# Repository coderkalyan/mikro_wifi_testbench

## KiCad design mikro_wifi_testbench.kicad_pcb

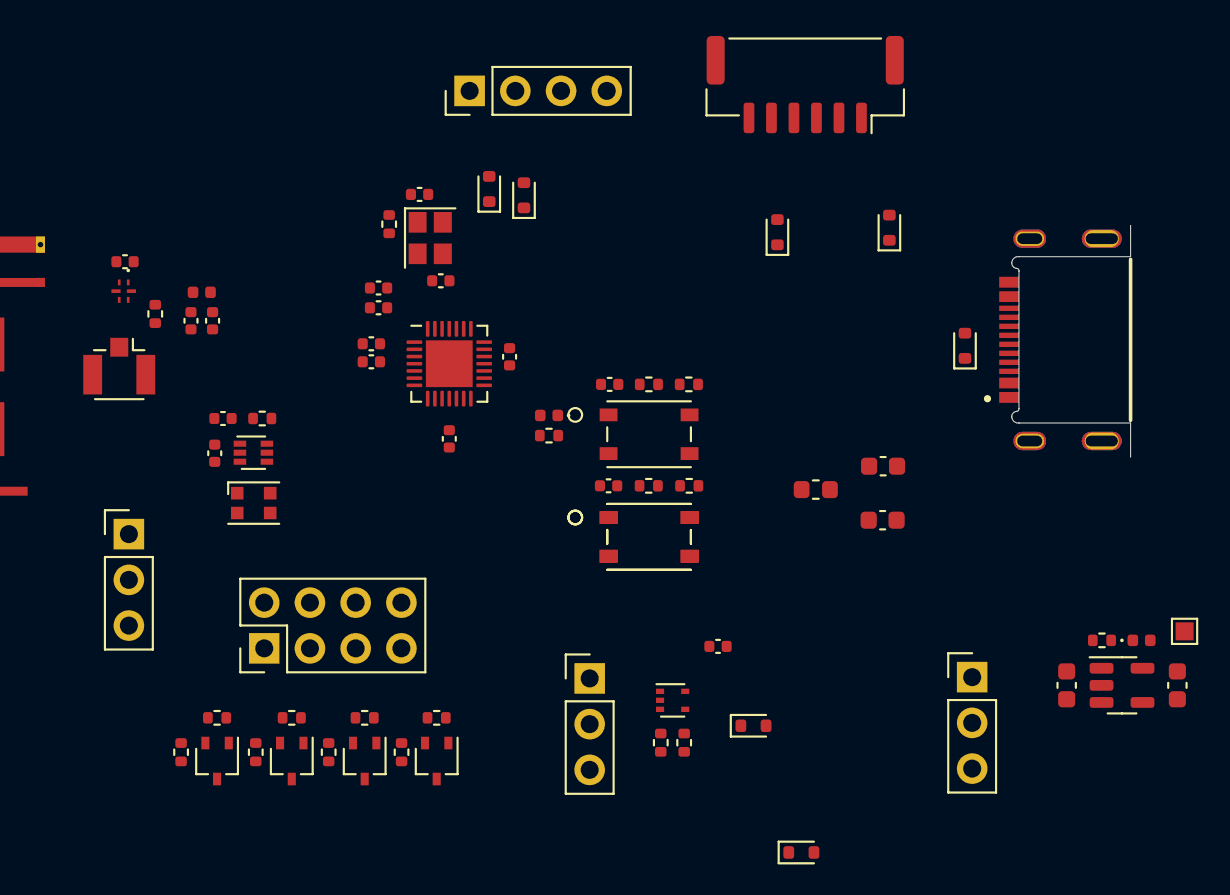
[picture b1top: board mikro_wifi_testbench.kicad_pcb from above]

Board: 2 copper layers, 74 parts (0 on the bottom side), 40 nets, no tracks yet.

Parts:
C1, C3: 0u1; C_0603_1608Metric
C2, C4, C5, C6, C7, C14, C16, C17, C19: 0u1; C_0402_1005Metric
C8: 1u; C_0402_1005Metric
C9, C11: 10p; C_0402_1005Metric
C10, C15: 10n; C_0402_1005Metric
C12, C13: 3p3; C_0402_1005Metric
C18, C20: 4u7; C_0603_1608Metric
D1, D3, D5, D6, D7: PESD3V3S1UB,115; D_SOD-523
D2: GREEN; LED_0402_1005Metric
D4: WS2812B; LED_WS2812B-2020_PLCC4_2.0x2.0mm
D8: LED; LED_0402_1005Metric
D9: D_Small; D_SOD-523
D10: D_Schottky; D_SOD-523
J1: IO; PinHeader_1x04_P2.54mm_Vertical
J2: LED; PinHeader_1x03_P2.54mm_Vertical
J3: PWR; PinHeader_1x03_P2.54mm_Vertical
J4: TLM; JST_GH_SM06B-GHS-TB_1x06-1MP_P1.25mm_Horizontal
J5: PCB_Antenna; Texas_SWRA117D_2.4GHz_Left
J6: U.FL; U.FL_Hirose_U.FL-R-SMT-1_Vertical
J8: SBUS; PinHeader_1x03_P2.54mm_Vertical
J10: USB_C_Receptacle_USB2.0; GCT_USB4510-03-1-A_REVA
J13: Conn_02x04_Odd_Even; PinHeader_2x04_P2.54mm_Vertical
L1: 2n2; L_0402_1005Metric
L2: 1u; L_0603_1608Metric
Q1, Q2, Q3, Q4: CJ2302; SOT-323_SC-70
R1, R2, R4, R7, R8, R11, R13, R14, R16, R18: 10K; R_0402_1005Metric
R3, R12, R15, R17: 100; R_0402_1005Metric
R5, R19: 1K5; R_0402_1005Metric
R6: 22; R_0402_1005Metric
R9: 0; R_0402_1005Metric
R10: 100K; R_0402_1005Metric
SW1, SW1#2, SW2: SW_Push; PTS815 SJM 250 SMTR LFS
TP1: 3V3; TestPoint_Pad_1.0x1.0mm
U1: SN74LVC1T45DRL; SOT-563
U3: TLV71333PDBV; SOT-23-5
U4: SKY13453-385LF; IC_SKY13453-385LF
U5: SN74LVC1G14DRL; SOT-553
U6: QFN-28-1EP_4x4mm_P0.4mm_EP2.6x2.6mm
Y1: 40MHz; Crystal_SMD_2520-4Pin_2.5x2.0mm

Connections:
+3V3: C3.1, C4.1, C5.1, C6.1, C7.1, C8.1, C10.1, C14.2, C15.1, C17.1, D2.2 (A), J1.1, J2.2, J3.3, R2.1, R7.1, R11.1, TP1.1, U1.6 (VCCB), U3.5 (OUT), U4.1 (VDD), U5.5 (VCC), U6.2 (VDD3P3), U6.3 (VDD3P3), U6.11 (VDD_RTC), U6.17 (VDD_CPU), U6.27 (VDDA), U6.28 (VDDA)
+5V: C18.1, D9.2 (A), D10.1 (K), J3.1, L2.1
/BOOT: C19.1, R13.2, U6.15 (GPIO9)
/Interfaces/NEOPIXEL: D4.4 (DIN), U1.3 (A)
/Interfaces/SBUS_IN: D7.1 (K), J8.1, R9.1, U5.2
/LED_STATUS: D8.2 (A), U6.16 (GPIO10)
/LNA: C12.1, L1.1, U6.1 (LNA_IN)
/LNA_IPEX: J6.1, U4.4 (RF2)
/LNA_PCB: J5.1, U4.2 (RF1)
/MOTOR1: J13.1, R3.1, U6.9 (GPIO4)
/MOTOR2: J13.3, R12.1, U6.10 (GPIO5)
/MOTOR3: J13.5, R15.1, U6.12 (GPIO6)
/MOTOR4: J13.7, R17.1, U6.13 (GPIO7)
/NEOPIXEL_3V3: U1.4 (B), U6.8 (GPIO3)
/RF_SW: R11.2, U4.5 (VCTL), U6.4 (GPIO0)
/SBUS: R9.2, R10.1, U5.4, U6.14 (GPIO8)
/UART0_RX_IO: D3.1 (K), J1.2, U6.23 (GPIO20)
/UART0_TX_IO: D1.1 (K), J1.3, U6.24 (GPIO21)
/UART1_RX_TELEM: D5.1 (K), J4.3, U6.6 (GPIO2)
/UART1_TX_TELEM: D6.1 (K), J4.2, U6.5 (GPIO1)
/USB_DN: J10.A7 (D-), J10.B7 (D-), U6.21 (GPIO18)
/USB_DP: J10.A6 (D+), J10.B6 (D+), U6.22 (GPIO19)
/XIN: R6.1, U6.26 (XTAL_P)
/XOUT: C11.1, U6.25 (XTAL_N), Y1.3
/nRST: C2.1, R4.2, U6.7 (CHIP_EN)
GND: C1.2, C2.2, C3.2, C4.2, C5.2, C6.2, C7.2, C8.2, C9.1, C10.2, C11.2, C12.2, C13.2, C14.1, C15.2, C16.1, C17.2, C18.2, C19.2, C20.2, D1.2 (A), D3.2 (A), D4.3 (VSS), D5.2 (A), D6.2 (A), D7.2 (A), J1.4, J2.3, J3.2, J4.6, J5.2, J6.2, J8.3, J13.2, J13.4, J13.6, J13.8, Q1.1 (S), Q2.1 (S), Q3.1 (S), Q4.1 (S), R1.1, R5.2, R8.2, R10.2, R14.2, R16.2, R18.2, R19.2, SW1.1, SW1#2.1, SW2.1, U1.2 (GND), U3.2 (GND), U4.3 (GND), U5.3 (GND), U6.29 (GND), Y1.2, Y1.4
unnamed: C9.2, R6.2, Y1.1
unnamed: D2.1 (K), R5.1
unnamed: D4.2 (DOUT), J2.1
unnamed: D8.1 (K), R19.1
unnamed: D9.1 (K), J8.2
unnamed: Q1.2 (G), R3.2, R8.1
unnamed: Q2.2 (G), R12.2, R14.1
unnamed: Q3.2 (G), R15.2, R16.1
unnamed: Q4.2 (G), R17.2, R18.1
unnamed: R2.2, R4.1, SW1.2, SW1#2.2
unnamed: R7.2, R13.1, SW2.2
unnamed: R1.2, U1.5 (DIR)
unnamed: C13.1, L1.2, U4.6 (RFC)
VDD: C1.1, C16.2, C20.1, D4.1 (VDD), J4.1, L2.2, U1.1 (VCCA), U3.1 (IN), U3.3 (EN)

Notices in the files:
parts and their libraries:
Copyright 2021 Accelerated Designs. All rights reserved.
